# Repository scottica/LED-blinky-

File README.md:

# Astable multivibrator PCB

## 📌 Overview
This repository contains the schematics, board layouts, and documentation for a custom, battery-powered LED blinker circuit. This project demonstrates an end-to-end hardware design process, from foundational circuit theory and simulation to a fully manufacturable Printed Circuit Board (PCB).

## ⚙️ Hardware & Circuit Design
At the core of this project is a discrete-transistor astable multivibrator circuit.

Core Logic: The design utilizes a two-transistor setup featuring 2N3904 NPN Bipolar Junction Transistors (BJTs).

Timing & Control: The alternating blink rate is dictated by precise RC timing networks and optimized current-limiting resistors.

PCB Features: The final board layout includes integrated power regulation, physical switch control, the LED arrays, and structural mounting holes for secure enclosure placement.

## 🚀 Project Process & Results

What: Designed and simulated a battery-powered LED blinker circuit before implementing it as a custom PCB.

How: Created a complete schematic and routed the PCB layout entirely within KiCad. The circuit operation was thoroughly validated through component selection and timing analysis.

Result: Successfully produced a functional PCB that reliably alternates LED blinking at a predictable and stable rate.

## 🛠️ Tools & Technologies Used

EDA Software: KiCad 

Skills: PCB Design, Analog Electronics, Circuit Simulation, Hardware Troubleshooting

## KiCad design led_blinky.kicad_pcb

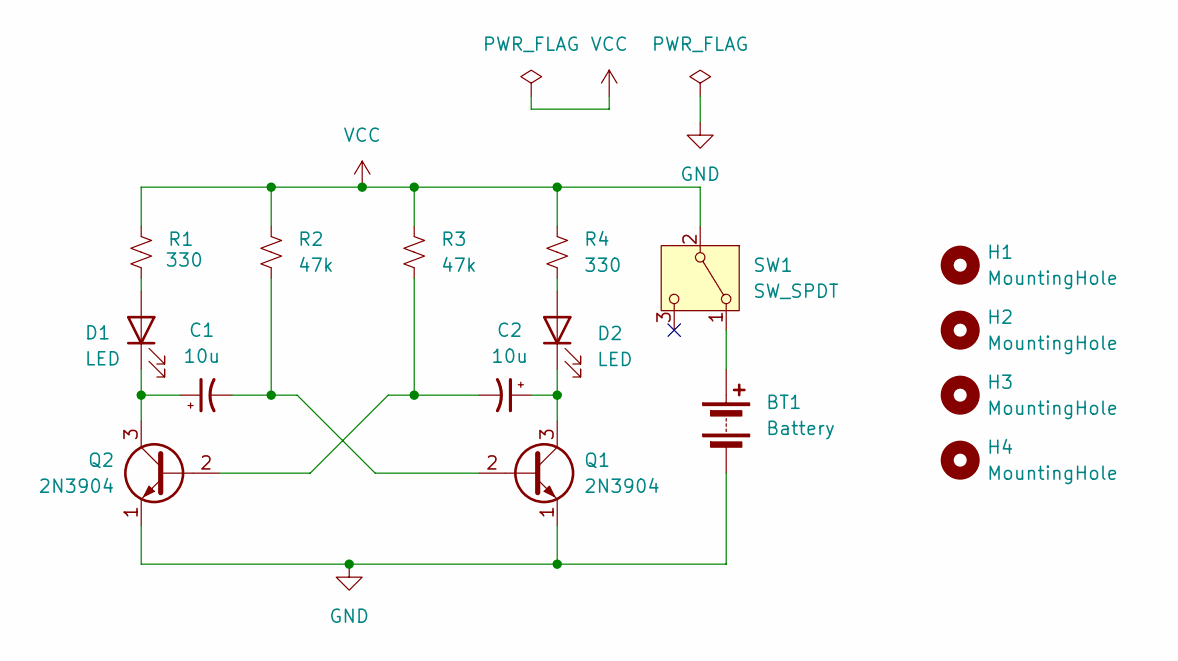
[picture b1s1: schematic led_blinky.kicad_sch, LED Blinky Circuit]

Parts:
BT1: Battery; BatteryHolder_Keystone_2479_3xAAA
C1, C2: 10u; CP_Radial_D6.3mm_P2.50mm
D1, D2: LED; LED_D5.0mm
H1, H2, H3, H4: MountingHole; MountingHole_3.2mm_M3
Q1, Q2: 2N3904; TO-92_Inline
R1, R4: 330; R_Axial_DIN0207_L6.3mm_D2.5mm_P10.16mm_Horizontal
R2, R3: 47k; R_Axial_DIN0207_L6.3mm_D2.5mm_P10.16mm_Horizontal
SW1: SW_SPDT; SW_E-Switch_EG1224_SPDT_Angled

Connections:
GND: BT1.2 (-), Q1.1 (E), Q2.1 (E)
unnamed: BT1.1 (+), SW1.1 (A)
unnamed: D1.2 (A), R1.2
unnamed: C1.1, D1.1 (K), Q2.3 (C)
unnamed: D2.2 (A), R4.2
unnamed: C2.1, D2.1 (K), Q1.3 (C)
unnamed: C1.2, Q1.2 (B), R2.2
unnamed: C2.2, Q2.2 (B), R3.2
VCC: R1.1, R2.1, R3.1, R4.1, SW1.2 (B)

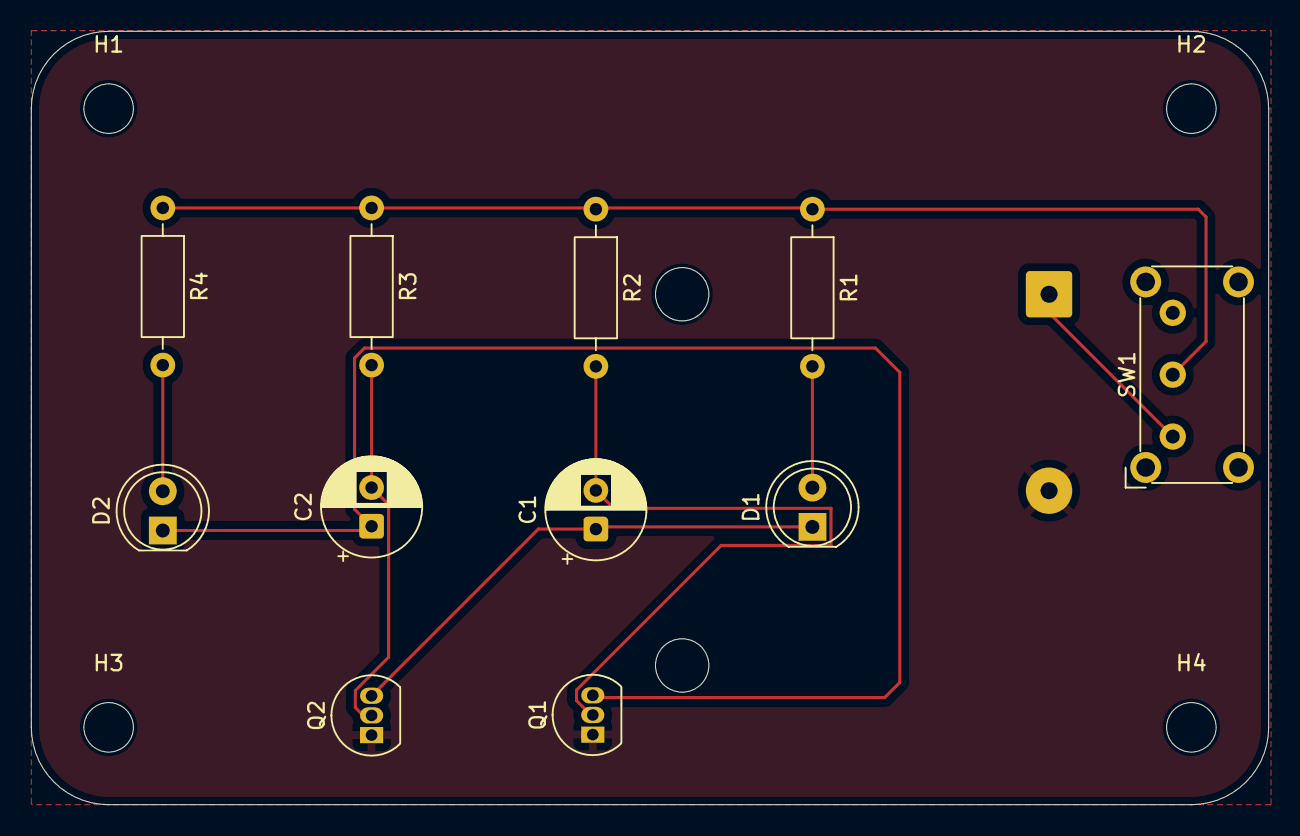
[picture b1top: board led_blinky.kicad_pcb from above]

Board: 2 copper layers, 80.0 x 50.0 mm, 16 parts (1 on the bottom side), 9 nets.

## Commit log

2026-02-14 Update README with new section headers and images
2026-02-14 Adjust image sizes in README
    Updated image tags to use a smaller width for screenshots.
2026-02-14 Increase image width in README
    Updated image tags to increase width from 200 to 250 pixels.
